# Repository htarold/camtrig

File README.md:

## What this is

Hack a PR3000 trail camera (camera trap) to add external trigger
functionality.  There are 2 options, _export_ the trigger (as
a master unit), or _accept_ it (as a slave unit).  This allows
multiple cameras to be connected together and be triggered
simultaneously, if one of them is a master, or by an external
switch.

This project is in beta, use at your own risk.

Not all trail cameras can be modified in the same way.  There needs
to be enough space to add the transmitter or receiver board, and
there must be space to add a connector in a weatherproof manner.
Here I repurpose the external battery jack for this purpose.

## Triggering in a trail camera

It is assumed that only cameras of the same make and model can share
triggers, since only then can it be guaranteed that they can
understand each other.  In practice, I have only ever seen triggers
signals that are active high, and they stay high for about 2 or 3
seconds.

The transmitter and receiver boards translate this signal between
active high/pushpull internally and active low/open drain externally.

### Tracing the signal path

In general, the PIR sensor outputs a signal that ultimately becomes
the trigger signal that will cause the camera to capture an image.
The trigger signal is active high (usually 3.3V), and stays high
for a few seconds (typically 2).

We want to be able to either insert our own trigger signal into
the existing signal path, or read this signal.  For this, we need
to trace the signal path starting at the PIR sensor’s output pin.

PIR sensors are easy to identify.  They are a through-hole component,
in a TO-5 metal can package, with a window.  They can have 3, 4,
or more pins.

### 4 or more pins
The
[BS412](https://cdn-shop.adafruit.com/product-files/4666/Datasheet.pdf)
is representative of this type.  Here,
the output pin is usually called REL (short for relay) or VOUT.
The sensor contains the relevant conditioning functionality,
so the REL pin outputs the TRIGGER signal to the MCU, no further
conditioning necessary.

The [PIR612](https://www.sunrom.com/get/751778) works similarly,
except it has 6 pins.  TRIGGER signal is on pin 5, VOUT.

First identify the REL pin on the PIR.  Trace this pin (using a
continuity tester) to a diode which will be close by.  There may
be an intervening low value resistor before the diode.

If the unit is to be a master, we want to connect the output of
this diode to the INT\_TRIG point on the transmitter circuit.
If the unit is to be a slave, connect the output of this diode to
the INT\_TRIG point on the receiver circuit instead.

### 3 pins
The [RE200](http://www.ladyada.net/media/sensors/RE200B.pdf)
and [D203S](https://www.allelectronics.com/mas_assets/media/allelectronics2018/spec/D203S.pdf)
are representative of this type.
The output pin is usually called Source or Output, and the output
signal is analog, not digital.  If the unit is to be a slave,
connect the Source pin to the INT\_TRIG point on the receiver
circuit (the transmitter board is not used).

The signal must therefore pass on to another chip such as the
[SGM8139](http://cn.sg-micro.com/uploads/soft/20200227/1582798839.pdf)
or [BISS0001](http://www.sc-tech.cn/en/BISS0001.pdf),
which conditions the signal to obtain the
digital trigger signal, which is routed to the MCU.

If the unit is to be a master, identify the Output pin of the
SGM8139/BISS0001 (pin 2).  This will be connected to 
INT\_TRIG of the transmitter board.

In all cases, the GND point on the transmitter and receiver boards
should be connected to any convenient ground pin on the CT board,
and the VCC point on the receiver board should be connected to a
3.3V pin on the CT board, such as the VDD pin on the PIR.

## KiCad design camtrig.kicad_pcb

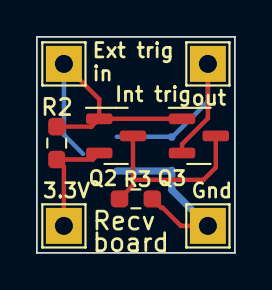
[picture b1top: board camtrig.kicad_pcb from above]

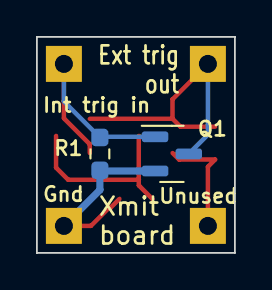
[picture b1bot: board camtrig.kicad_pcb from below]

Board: 2 copper layers, 11.0 x 12.0 mm, 10 parts (2 on the bottom side), 5 nets.

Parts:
Q1: 2N7002; SOT-23
Q2, Q3: BSS84; SOT-23
R1, R2, R3: 100k; R_0603_1608Metric_Pad0.98x0.95mm_HandSolder
TP4: xmit_recv_tp; TestPoint_THTPad_2.0x2.0mm_Drill1.0mm
TP5: GND_TP; TestPoint_THTPad_2.0x2.0mm_Drill1.0mm
TP6: TP6; TestPoint_THTPad_2.0x2.0mm_Drill1.0mm
TP7: TP7; TestPoint_THTPad_2.0x2.0mm_Drill1.0mm

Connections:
EXT_TRIG: Q1.3 (D), Q2.1 (G), Q3.1 (G), R2.2, TP4.1
GND: Q1.2 (S), R1.2, R3.1, TP5.1
INT_TRIG: Q1.1 (G), Q3.2 (S), R1.1, TP7.1
unnamed: Q2.3 (D), Q3.3 (D), R3.2
VCC: Q2.2 (S), R2.1, TP6.1

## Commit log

2022-09-17 Added(?) video link to README.md
2022-09-17 Added links to README
